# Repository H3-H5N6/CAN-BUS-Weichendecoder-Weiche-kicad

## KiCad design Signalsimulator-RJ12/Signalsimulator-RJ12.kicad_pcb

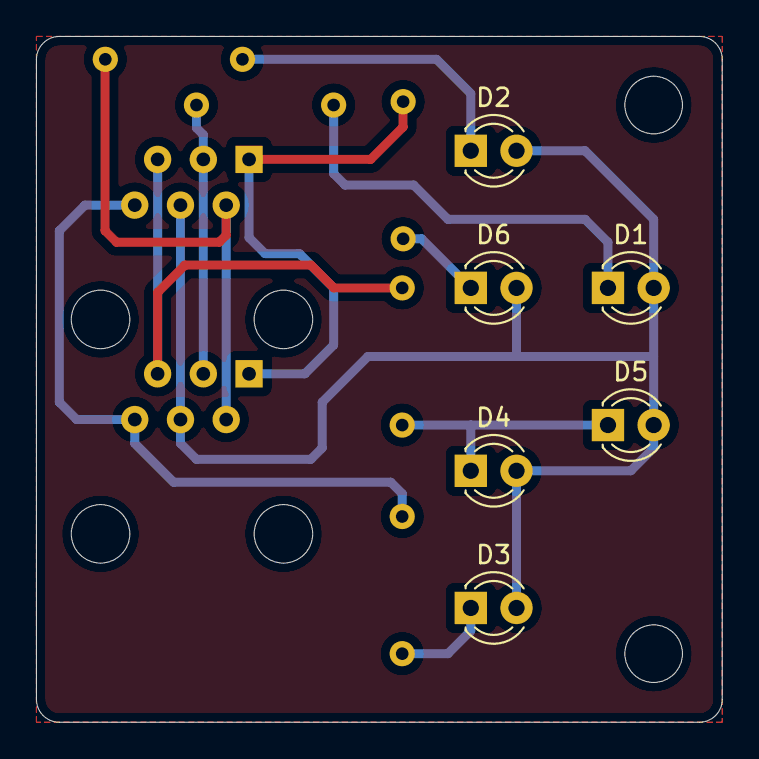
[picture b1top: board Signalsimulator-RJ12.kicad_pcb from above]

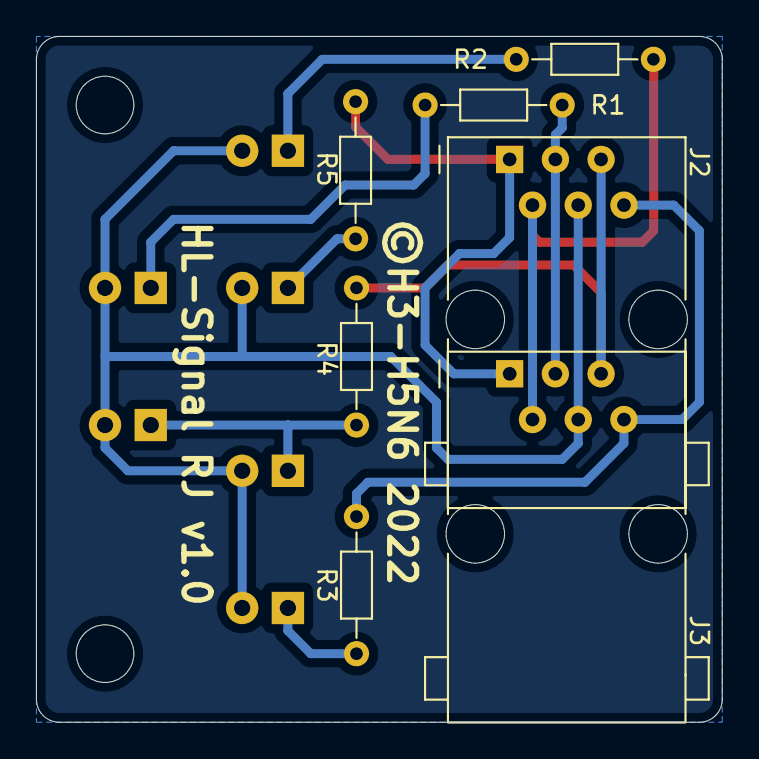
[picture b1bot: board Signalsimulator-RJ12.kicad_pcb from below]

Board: 2 copper layers, 38.1 x 38.1 mm, 15 parts (7 on the bottom side), 11 nets.

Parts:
3k3: R3; R_Axial_DIN0204_L3.6mm_D1.6mm_P7.62mm_Horizontal
D1: Rot 2; LED_D3.0mm
D2: Grün; LED_D3.0mm
D3: Gelb; LED_D3.0mm
D4, D5: Weiß; LED_D3.0mm
D6: Rot 1; LED_D3.0mm
H1, H1#2: MountingHole; MountingHole_3.2mm_M3
J2, J3: RJ12; RJ12_ECON
R1, R2, R5: 3k3; R_Axial_DIN0204_L3.6mm_D1.6mm_P7.62mm_Horizontal
R4: 2k2; R_Axial_DIN0204_L3.6mm_D1.6mm_P7.62mm_Horizontal

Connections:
+5P: D1.2 (A), D2.2 (A), D3.2 (A), D4.2 (A), D5.2 (A), D6.2 (A), J2.4, J3.4
unnamed: 3k3.1, D3.1 (K)
unnamed: 3k3.2, J2.6, J3.6
unnamed: D1.1 (K), R1.1
unnamed: D2.1 (K), R2.1
unnamed: D4.1 (K), D5.1 (K), R4.1
unnamed: D6.1 (K), R5.1
unnamed: J2.1, J3.1, R5.2
unnamed: J2.2, J3.2, R2.2
unnamed: J2.3, J3.3, R1.2
unnamed: J2.5, J3.5, R4.2

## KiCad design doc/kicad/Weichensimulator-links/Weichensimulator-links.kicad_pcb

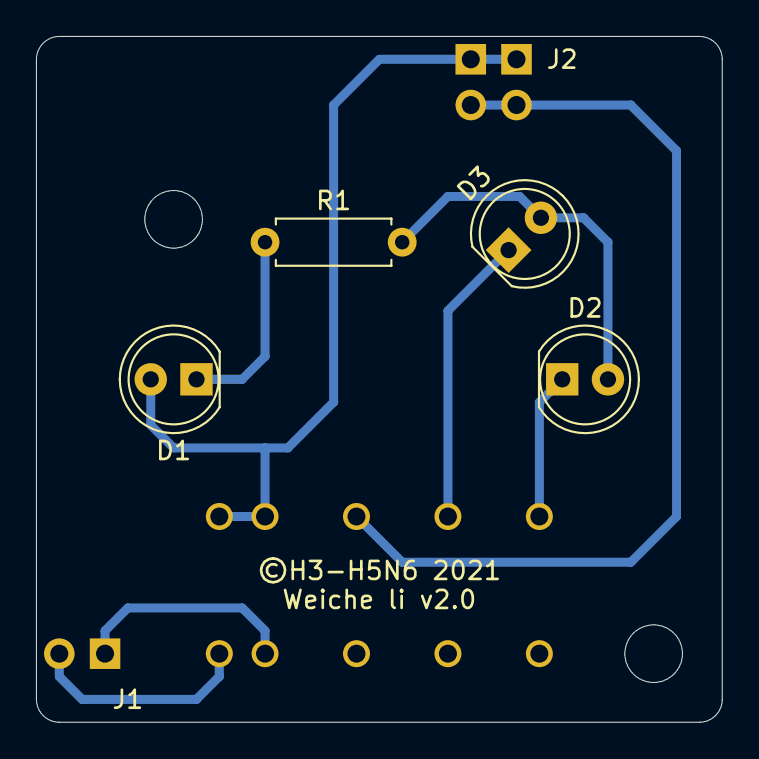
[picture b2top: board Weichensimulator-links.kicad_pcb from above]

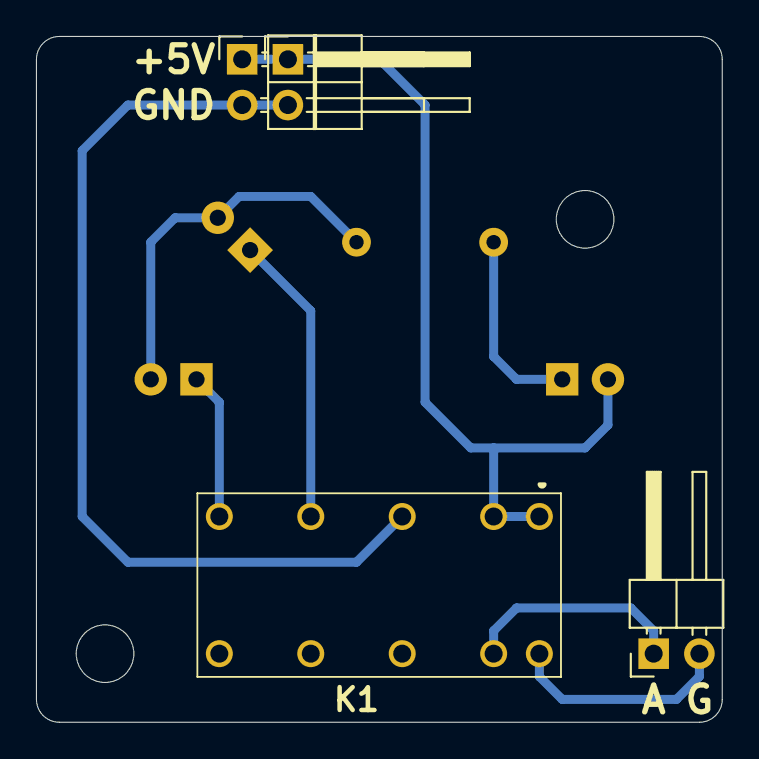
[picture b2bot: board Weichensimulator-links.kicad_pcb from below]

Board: 2 copper layers, 38.1 x 38.1 mm, 10 parts (4 on the bottom side), 8 nets.

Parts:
D1, D2, D3: LED; LED_D5.0mm
H1, H1#2: MountingHole; MountingHole_3.2mm_M3
J1, J3: Conn_01x02_Male; Pin_Header_Angled_1x02_Pitch2.54mm
J2: Power; Pin_Header_Angled_1x02_Pitch2.54mm
K1: HFD2_005-S-L2-D; HFD2005SL2D
R1: 100; R_Axial_DIN0207_L6.3mm_D2.5mm_P7.62mm_Horizontal

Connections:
+5V: D1.2, J2.1, J3.1, K1.1, K1.2
GND: J2.2, J3.2, K1.4
unnamed: D1.1, R1.1
unnamed: D2.1, K1.8
unnamed: D2.2, D3.2, R1.2
unnamed: D3.1, K1.6
unnamed: J1.1, K1.15
unnamed: J1.2, K1.16

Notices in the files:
Signalsimulator-RJ12/Signalsimulator-RJ12.kicad_pcb:
©H3-H5N6 2022
doc/kicad/Weichensimulator-links/Weichensimulator-links.kicad_pcb:
©H3-H5N6 2021
